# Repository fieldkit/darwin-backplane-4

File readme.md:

DARWIN-BACKPLANE

Experimental development repo for next-generation FieldKit hardware.

-- This hardware is experimental and still under development, the designs may contain errors. --

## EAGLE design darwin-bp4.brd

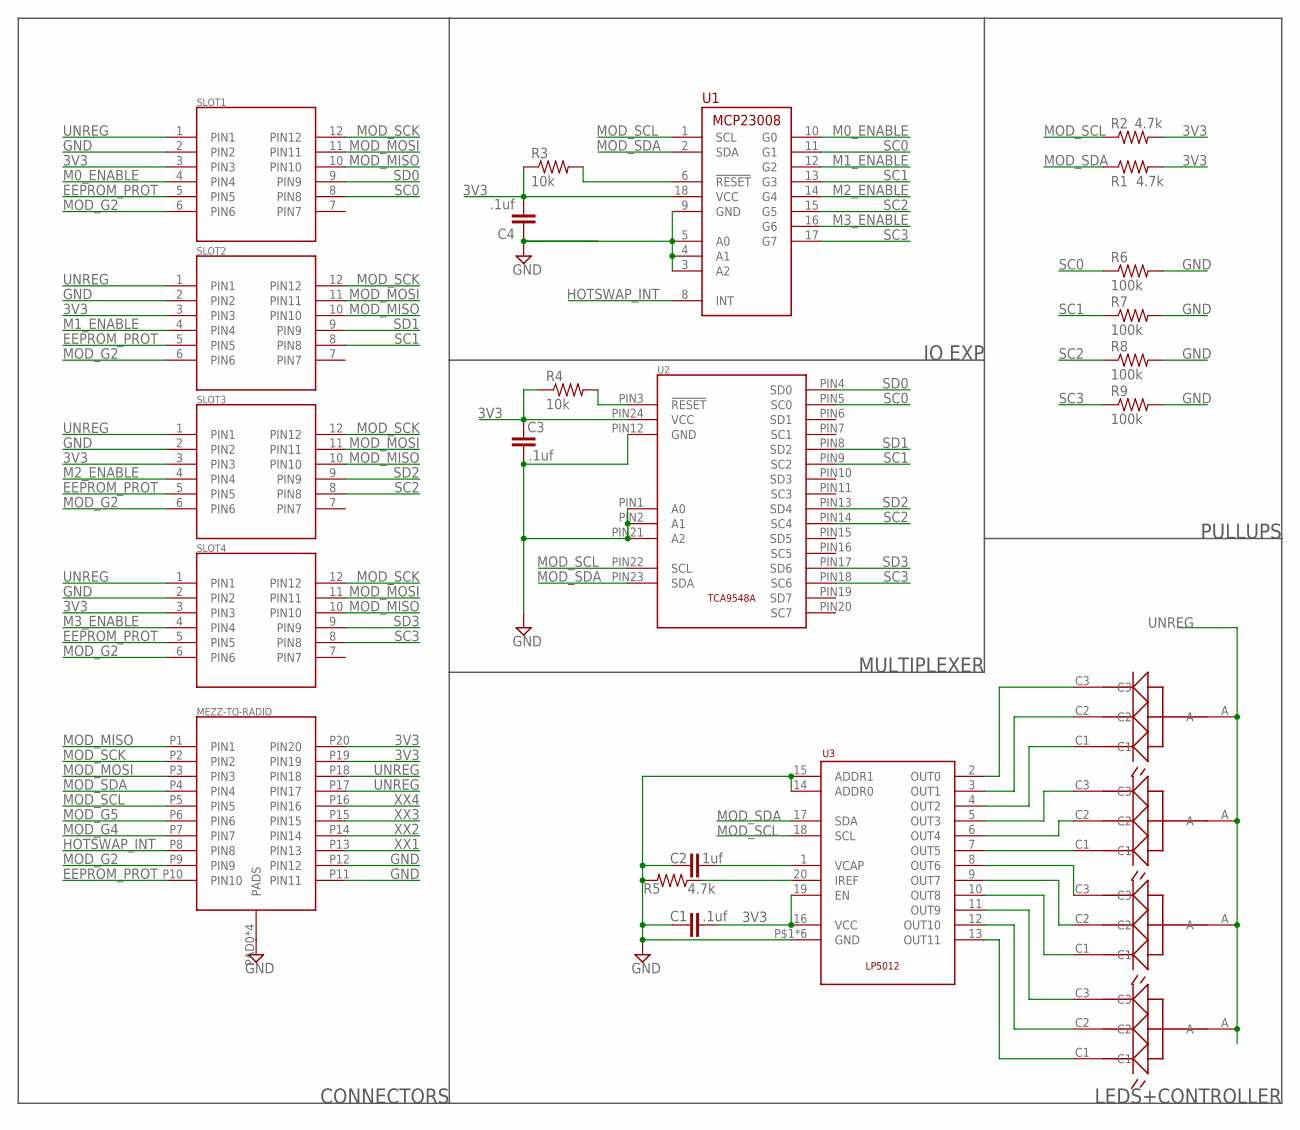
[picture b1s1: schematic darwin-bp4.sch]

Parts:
C1, C3, C4: .1uf; C0603K
C2: 1uf; C0603K
MEZZ-TO-RADIO: M55-6102042R7102(M); M55-7102042R
R1, R2, R5: 4.7k; R0603
R3, R4: 10k; R0603
R6, R7, R8, R9: 100k; R0603
SLOT1, SLOT2, SLOT3, SLOT4: 2X6-HEADERSDS; 12PH
U1: MCP23008; SOIC18-W
U2: TCA9548A; TSSOP-24
U3: LP5012; QFN40P300X300X80-20N
U$1, U$2, U$3, U$4: CLMVC-FKC-CGJJM569ABB7A343; 2MMPLCC4

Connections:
3V3: C1.2, C3.2, C4.2, MEZZ-TO-RADIO.P19 (PIN19), MEZZ-TO-RADIO.P20 (PIN20), R1.2, R2.2, R3.1, R4.1, SLOT1.3 (PIN3), SLOT2.3 (PIN3), SLOT3.3 (PIN3), SLOT4.3 (PIN3), U1.18 (VCC), U2.PIN24 (VCC), U3.16 (VCC), U3.19 (EN)
!RESET: R3.2, U1.6 (!RESET)
EEPROM_PROT: MEZZ-TO-RADIO.P10 (PIN10), SLOT1.5 (PIN5), SLOT2.5 (PIN5), SLOT3.5 (PIN5), SLOT4.5 (PIN5)
GND: C1.1, C2.1, C3.1, C4.1, MEZZ-TO-RADIO.P11 (PIN11), MEZZ-TO-RADIO.P12 (PIN12), MEZZ-TO-RADIO.PAD0 (PADS), MEZZ-TO-RADIO.PAD1 (PADS), MEZZ-TO-RADIO.PAD2 (PADS), MEZZ-TO-RADIO.PAD3 (PADS), R5.2, R6.2, R7.2, R8.2, R9.2, SLOT1.2 (PIN2), SLOT2.2 (PIN2), SLOT3.2 (PIN2), SLOT4.2 (PIN2), U1.3 (A2), U1.4 (A1), U1.5 (A0), U1.9 (GND), U2.PIN1 (A0), U2.PIN2 (A1), U2.PIN12 (GND), U2.PIN21 (A2), U3.14 (ADDR0), U3.15 (ADDR1), U3.P$1 (GND), U3.P$2 (GND), U3.P$3 (GND), U3.P$4 (GND), U3.P$5 (GND), U3.P$6 (GND)
HOTSWAP_INT: MEZZ-TO-RADIO.P8 (PIN8), U1.8 (INT)
M0_ENABLE: SLOT1.4 (PIN4), U1.10 (G0)
M1_ENABLE: SLOT2.4 (PIN4), U1.12 (G2)
M2_ENABLE: SLOT3.4 (PIN4), U1.14 (G4)
M3_ENABLE: SLOT4.4 (PIN4), U1.16 (G6)
MOD_G2: MEZZ-TO-RADIO.P9 (PIN9), SLOT1.6 (PIN6), SLOT2.6 (PIN6), SLOT3.6 (PIN6), SLOT4.6 (PIN6)
MOD_G4: MEZZ-TO-RADIO.P7 (PIN7)
MOD_G5: MEZZ-TO-RADIO.P6 (PIN6)
MOD_MISO: MEZZ-TO-RADIO.P1 (PIN1), SLOT1.10 (PIN10), SLOT2.10 (PIN10), SLOT3.10 (PIN10), SLOT4.10 (PIN10)
MOD_MOSI: MEZZ-TO-RADIO.P3 (PIN3), SLOT1.11 (PIN11), SLOT2.11 (PIN11), SLOT3.11 (PIN11), SLOT4.11 (PIN11)
MOD_SCK: MEZZ-TO-RADIO.P2 (PIN2), SLOT1.12 (PIN12), SLOT2.12 (PIN12), SLOT3.12 (PIN12), SLOT4.12 (PIN12)
MOD_SCL: MEZZ-TO-RADIO.P5 (PIN5), R2.1, U1.1 (SCL), U2.PIN22 (SCL), U3.18 (SCL)
MOD_SDA: MEZZ-TO-RADIO.P4 (PIN4), R1.1, U1.2 (SDA), U2.PIN23 (SDA), U3.17 (SDA)
unnamed: U3.2 (OUT0), U$1.C3
unnamed: R4.2, U2.PIN3 (!RESET)
unnamed: U3.3 (OUT1), U$1.C2
unnamed: U3.4 (OUT2), U$1.C1
unnamed: U3.5 (OUT3), U$2.C3
unnamed: U3.6 (OUT4), U$2.C2
unnamed: U3.7 (OUT5), U$2.C1
unnamed: U3.8 (OUT6), U$3.C3
unnamed: U3.9 (OUT7), U$3.C2
unnamed: U3.10 (OUT8), U$3.C1
unnamed: U3.11 (OUT9), U$4.C3
unnamed: U3.12 (OUT10), U$4.C2
unnamed: U3.13 (OUT11), U$4.C1
unnamed: C2.2, U3.1 (VCAP)
unnamed: R5.1, U3.20 (IREF)
SC0: R6.1, SLOT1.8 (PIN8), U1.11 (G1), U2.PIN5 (SC0)
SC1: R7.1, SLOT2.8 (PIN8), U1.13 (G3), U2.PIN9 (SC2)
SC2: R8.1, SLOT3.8 (PIN8), U1.15 (G5), U2.PIN14 (SC4)
SC3: R9.1, SLOT4.8 (PIN8), U1.17 (G7), U2.PIN18 (SC6)
SD0: SLOT1.9 (PIN9), U2.PIN4 (SD0)
SD1: SLOT2.9 (PIN9), U2.PIN8 (SD2)
SD2: SLOT3.9 (PIN9), U2.PIN13 (SD4)
SD3: SLOT4.9 (PIN9), U2.PIN17 (SD6)
UNREG: MEZZ-TO-RADIO.P17 (PIN17), MEZZ-TO-RADIO.P18 (PIN18), SLOT1.1 (PIN1), SLOT2.1 (PIN1), SLOT3.1 (PIN1), SLOT4.1 (PIN1), U$1.A, U$2.A, U$3.A, U$4.A
XX1: MEZZ-TO-RADIO.P13 (PIN13)
XX2: MEZZ-TO-RADIO.P14 (PIN14)
XX3: MEZZ-TO-RADIO.P15 (PIN15)
XX4: MEZZ-TO-RADIO.P16 (PIN16)

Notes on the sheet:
IO EXP
MULTIPLEXER
LEDS+CONTROLLER
PULLUPS
CONNECTORS

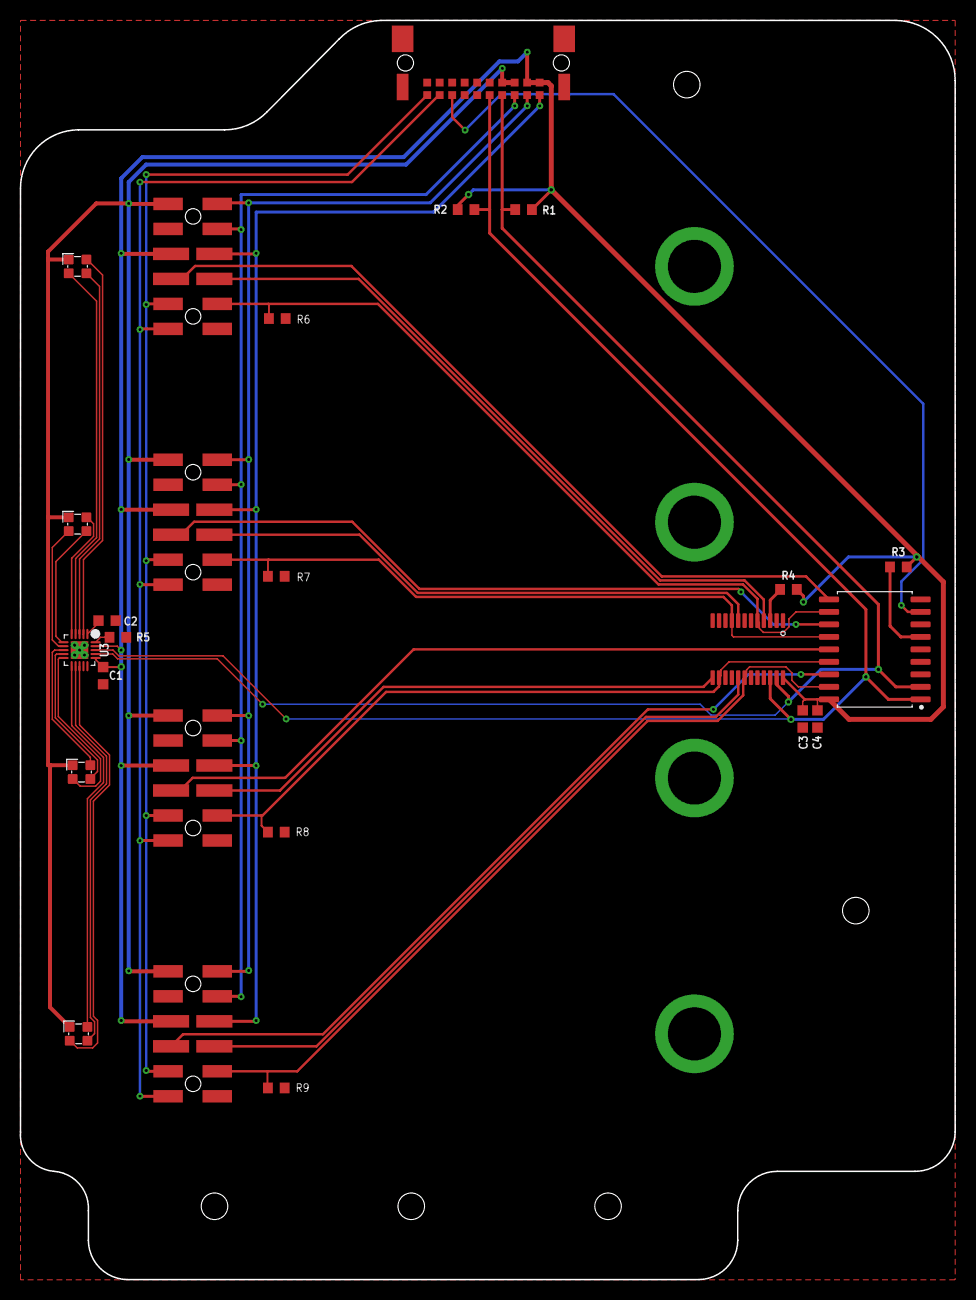
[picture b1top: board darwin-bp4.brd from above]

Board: 4 copper layers, 95.0 x 128.0 mm, 25 parts (0 on the bottom side), 39 nets.

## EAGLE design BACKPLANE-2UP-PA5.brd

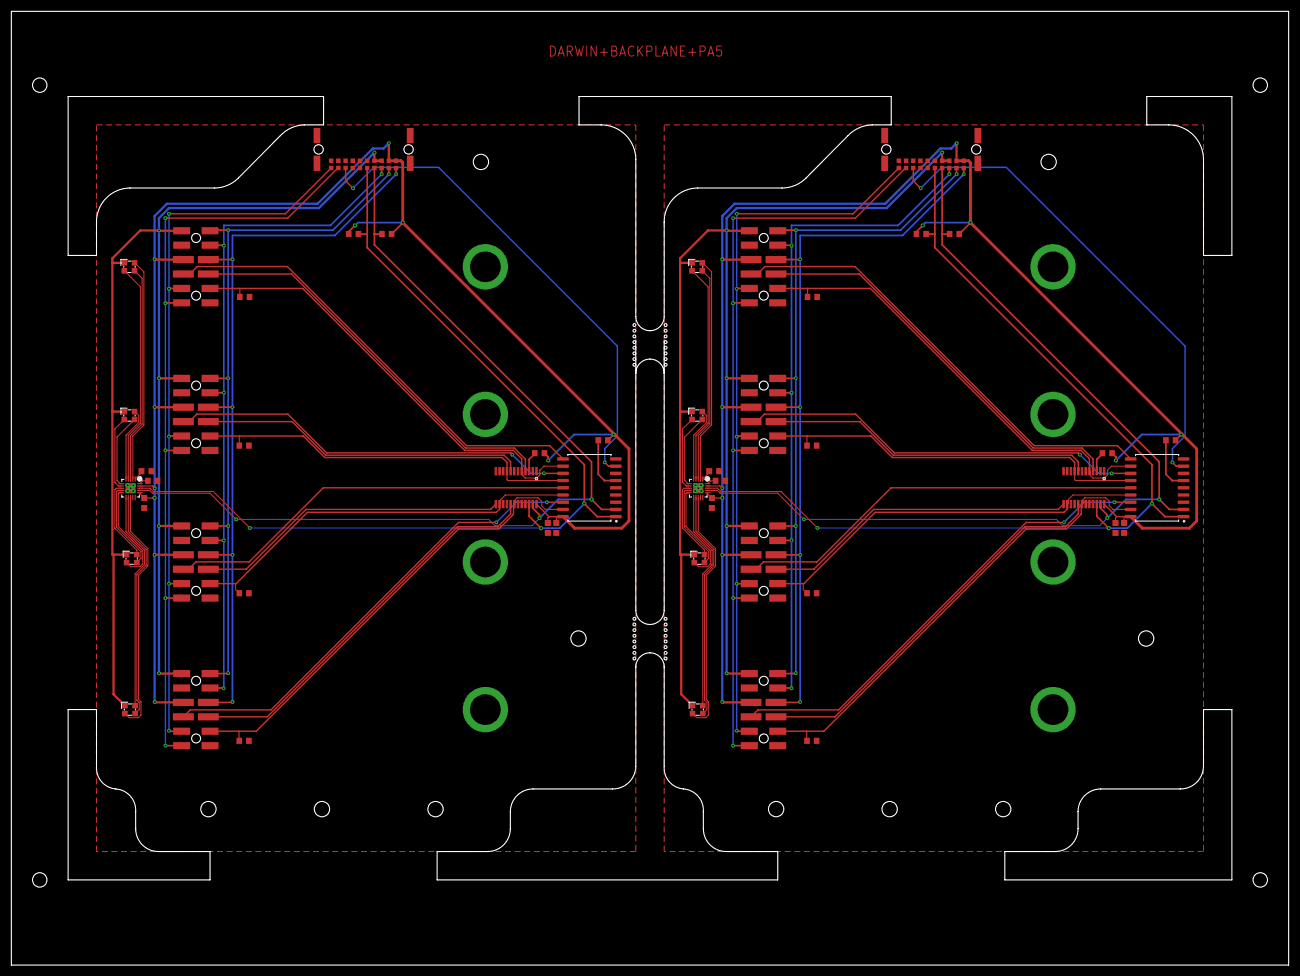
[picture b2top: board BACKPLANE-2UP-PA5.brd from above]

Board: 2 copper layers, 225.0 x 168.0 mm, 50 parts (0 on the bottom side), 78 nets.

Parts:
C1, C5: .1u; C0603K
C2, C6: 1u; C0603K
C3, C4, C7, C8: .1uf; C0603K
MEZZ-TO-RADIO, MEZZ-TO-RADIO1: M55-6102042R7102(M); M55-7102042R
R1, R2, R10, R11: 4.7k; R0603
R3, R4, R12, R13: 10k; R0603
R5, R14: R0603
R6, R7, R8, R9, R15, R16, R17, R18: 100k; R0603
SLOT1, SLOT2, SLOT3, SLOT4, SLOT5, SLOT6, SLOT7, SLOT8: 2X6-HEADERSDS; 12PH
U1, U4: MCP23008; SOIC18-W
U2, U5: TCA9548A; TSSOP-24
U3, U6: LP5012; QFN40P300X300X80-20N
U$1, U$2, U$3, U$4, U$5, U$6, U$7, U$8: CLMVC-FKC-CGJJM569ABB7A343; 2MMPLCC4

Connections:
3V1: C1.2, C3.2, C4.2, MEZZ-TO-RADIO.P19, MEZZ-TO-RADIO.P20, R1.2, R2.2, R3.1, R4.1, SLOT1.3, SLOT2.3, SLOT3.3, SLOT4.3, U1.18, U2.PIN24, U3.16, U3.19
3V2: C5.2, C7.2, C8.2, MEZZ-TO-RADIO1.P19, MEZZ-TO-RADIO1.P20, R10.2, R11.2, R12.1, R13.1, SLOT5.3, SLOT6.3, SLOT7.3, SLOT8.3, U4.18, U5.PIN24, U6.16, U6.19
!RESET: R3.2, U1.6
!RESET1: R12.2, U4.6
EEPROM_PROT1: MEZZ-TO-RADIO.P10, SLOT1.5, SLOT2.5, SLOT3.5, SLOT4.5
EEPROM_PROT2: MEZZ-TO-RADIO1.P10, SLOT5.5, SLOT6.5, SLOT7.5, SLOT8.5
GND: C1.1, C2.1, C3.1, C4.1, MEZZ-TO-RADIO.P11, MEZZ-TO-RADIO.P12, R5.2, R6.2, R7.2, R8.2, R9.2, SLOT1.2, SLOT2.2, SLOT3.2, SLOT4.2, U1.3, U1.4, U1.5, U1.9, U2.PIN1, U2.PIN2, U2.PIN12, U2.PIN21, U3.14, U3.15, U3.P$1, U3.P$2, U3.P$3, U3.P$4, U3.P$5, U3.P$6
GND1: C5.1, C6.1, C7.1, C8.1, MEZZ-TO-RADIO1.P11, MEZZ-TO-RADIO1.P12, R14.2, R15.2, R16.2, R17.2, R18.2, SLOT5.2, SLOT6.2, SLOT7.2, SLOT8.2, U4.3, U4.4, U4.5, U4.9, U5.PIN1, U5.PIN2, U5.PIN12, U5.PIN21, U6.14, U6.15, U6.P$1, U6.P$2, U6.P$3, U6.P$4, U6.P$5, U6.P$6
HOTSWAP_INT: MEZZ-TO-RADIO.P8, U1.8
HOTSWAP_INT1: MEZZ-TO-RADIO1.P8, U4.8
M0_ENABLE: SLOT1.4, U1.10
M0_ENABLE1: SLOT5.4, U4.10
M1_ENABLE: SLOT2.4, U1.12
M1_ENABLE1: SLOT6.4, U4.12
M2_ENABLE: SLOT3.4, U1.14
M2_ENABLE1: SLOT7.4, U4.14
M3_ENABLE: SLOT4.4, U1.16
M3_ENABLE1: SLOT8.4, U4.16
MOD_G1: MEZZ-TO-RADIO.P9, SLOT1.6, SLOT2.6, SLOT3.6, SLOT4.6
MOD_G3: MEZZ-TO-RADIO1.P9, SLOT5.6, SLOT6.6, SLOT7.6, SLOT8.6
MOD_MISO: MEZZ-TO-RADIO.P1, SLOT1.10, SLOT2.10, SLOT3.10, SLOT4.10
MOD_MISO1: MEZZ-TO-RADIO1.P1, SLOT5.10, SLOT6.10, SLOT7.10, SLOT8.10
MOD_MOSI: MEZZ-TO-RADIO.P3, SLOT1.11, SLOT2.11, SLOT3.11, SLOT4.11
MOD_MOSI1: MEZZ-TO-RADIO1.P3, SLOT5.11, SLOT6.11, SLOT7.11, SLOT8.11
MOD_SCK: MEZZ-TO-RADIO.P2, SLOT1.12, SLOT2.12, SLOT3.12, SLOT4.12
MOD_SCK1: MEZZ-TO-RADIO1.P2, SLOT5.12, SLOT6.12, SLOT7.12, SLOT8.12
MOD_SCL: MEZZ-TO-RADIO.P5, R2.1, U1.1, U2.PIN22, U3.18
MOD_SCL1: MEZZ-TO-RADIO1.P5, R11.1, U4.1, U5.PIN22, U6.18
MOD_SDA: MEZZ-TO-RADIO.P4, R1.1, U1.2, U2.PIN23, U3.17
MOD_SDA1: MEZZ-TO-RADIO1.P4, R10.1, U4.2, U5.PIN23, U6.17
unnamed: U3.2, U$1.C3
unnamed: R4.2, U2.PIN3
unnamed: U3.3, U$1.C2
unnamed: U3.4, U$1.C1
unnamed: U3.5, U$2.C3
unnamed: U3.6, U$2.C2
unnamed: U3.7, U$2.C1
unnamed: U3.8, U$3.C3
unnamed: U3.9, U$3.C2
unnamed: R13.2, U5.PIN3
unnamed: U3.10, U$3.C1
unnamed: U3.11, U$4.C3
unnamed: U3.12, U$4.C2
unnamed: U3.13, U$4.C1
unnamed: U6.2, U$5.C3
unnamed: U6.3, U$5.C2
unnamed: U6.4, U$5.C1
unnamed: U6.5, U$6.C3
unnamed: U6.6, U$6.C2
unnamed: C2.2, U3.1
unnamed: R5.1, U3.20
unnamed: U6.7, U$6.C1
unnamed: U6.8, U$7.C3
unnamed: U6.9, U$7.C2
unnamed: U6.10, U$7.C1
unnamed: U6.11, U$8.C3
unnamed: U6.12, U$8.C2
unnamed: U6.13, U$8.C1
unnamed: C6.2, U6.1
unnamed: R14.1, U6.20
SC0: R6.1, SLOT1.8, U1.11, U2.PIN5
SC1: R7.1, SLOT2.8, U1.13, U2.PIN9
SC2: R8.1, SLOT3.8, U1.15, U2.PIN14
SC3: R9.1, SLOT4.8, U1.17, U2.PIN18
SC4: R15.1, SLOT5.8, U4.11, U5.PIN5
SC5: R16.1, SLOT6.8, U4.13, U5.PIN9
SC6: R17.1, SLOT7.8, U4.15, U5.PIN14
SC7: R18.1, SLOT8.8, U4.17, U5.PIN18
SD0: SLOT1.9, U2.PIN4
SD1: SLOT2.9, U2.PIN8
SD2: SLOT3.9, U2.PIN13
SD3: SLOT4.9, U2.PIN17
SD4: SLOT5.9, U5.PIN4
SD5: SLOT8.9, U5.PIN17
SD6: SLOT7.9, U5.PIN13
SD7: SLOT6.9, U5.PIN8
UNREG: MEZZ-TO-RADIO.P17, MEZZ-TO-RADIO.P18, SLOT1.1, SLOT2.1, SLOT3.1, SLOT4.1, U$1.A, U$2.A, U$3.A, U$4.A
UNREG1: MEZZ-TO-RADIO1.P17, MEZZ-TO-RADIO1.P18, SLOT5.1, SLOT6.1, SLOT7.1, SLOT8.1, U$5.A, U$6.A, U$7.A, U$8.A

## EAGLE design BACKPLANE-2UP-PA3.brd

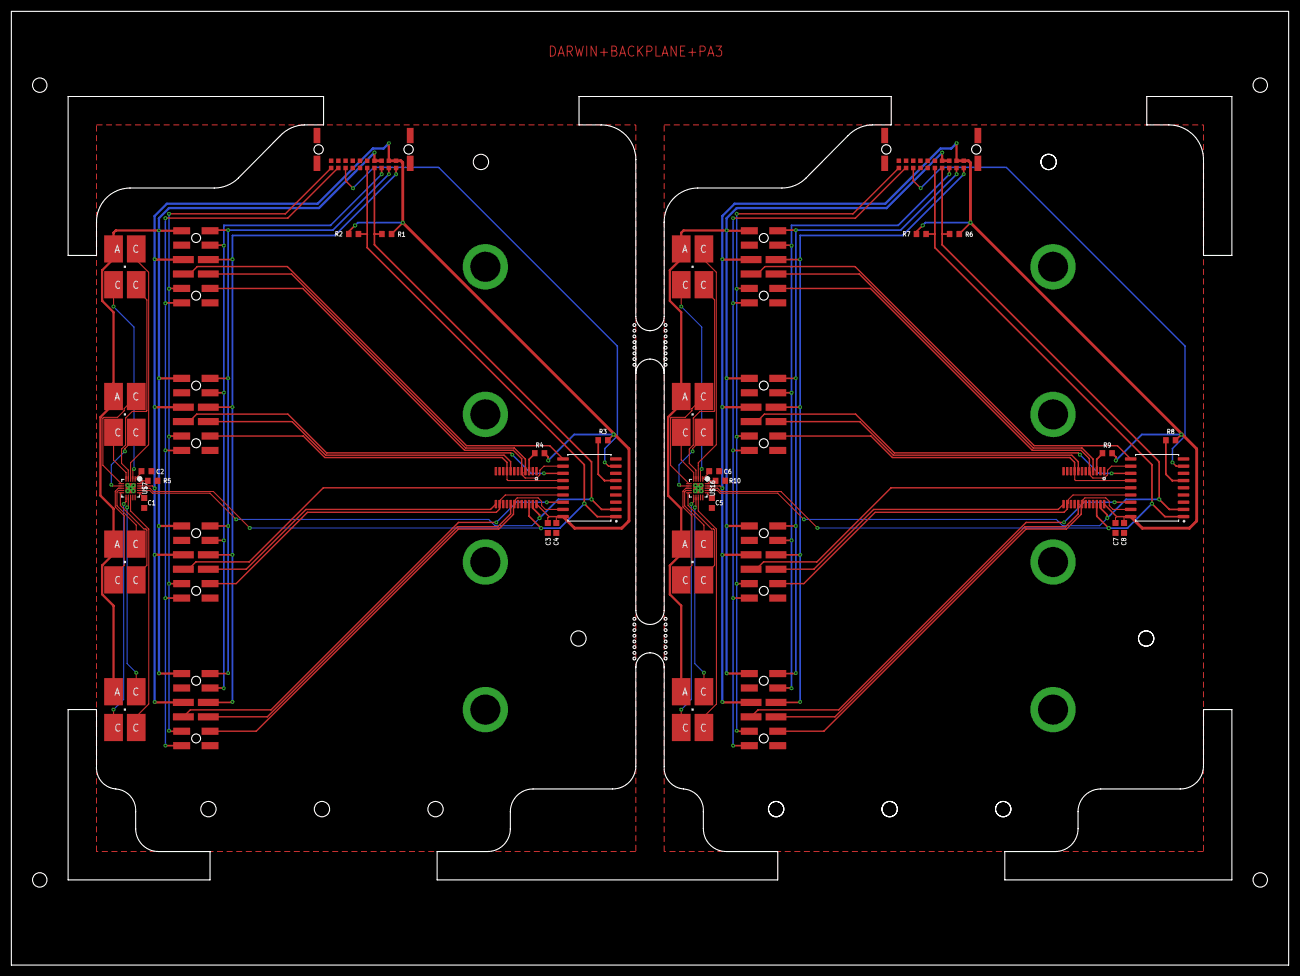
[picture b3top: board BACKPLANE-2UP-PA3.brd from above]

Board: 2 copper layers, 225.0 x 168.0 mm, 42 parts (0 on the bottom side), 78 nets.

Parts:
C1, C5: .1u; C0603K
C2, C3, C4, C6, C7, C8: 1u; C0603K
LED1, LED2, LED3, LED4, LED5, LED6, LED7, LED8: P-LCC-4
R1, R2, R6, R7: 4.7k; R0603
R3, R4, R8, R9: 10k; R0603
R5, R10: R0603
U$1, U$9: MCP23008; SOIC18-W
U$2, U$3, U$4, U$5, U$10, U$11, U$12, U$14: 2X6-HEADERSDS; 12PH
U$6, U$15: TCA9548A; TSSOP-24
U$7, U$16: LP5012; QFN40P300X300X80-20N
U$8, U$13: M55-6102042R7102(M); M55-7102042R

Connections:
3V1: C1.2, C3.2, C4.2, R1.2, R2.2, R3.1, R4.1, U$1.18, U$2.3, U$3.3, U$4.3, U$5.3, U$6.PIN24, U$7.16, U$7.19, U$13.P19, U$13.P20
3V2: C5.2, C7.2, C8.2, R6.2, R7.2, R8.1, R9.1, U$8.P19, U$8.P20, U$9.18, U$10.3, U$11.3, U$12.3, U$14.3, U$15.PIN24, U$16.16, U$16.19
!RESET: R3.2, U$1.6
!RESET1: R8.2, U$9.6
EEPROM_PROT1: U$2.5, U$3.5, U$4.5, U$5.5, U$13.P10
EEPROM_PROT2: U$8.P10, U$10.5, U$11.5, U$12.5, U$14.5
GND: C1.1, C2.1, C3.1, C4.1, R5.2, U$1.3, U$1.4, U$1.5, U$1.9, U$2.2, U$3.2, U$4.2, U$5.2, U$6.PIN1, U$6.PIN2, U$6.PIN12, U$6.PIN21, U$7.14, U$7.15, U$7.P$1, U$7.P$2, U$7.P$3, U$7.P$4, U$7.P$5, U$7.P$6, U$13.P11, U$13.P12
GND1: C5.1, C6.1, C7.1, C8.1, R10.2, U$8.P11, U$8.P12, U$9.3, U$9.4, U$9.5, U$9.9, U$10.2, U$11.2, U$12.2, U$14.2, U$15.PIN1, U$15.PIN2, U$15.PIN12, U$15.PIN21, U$16.14, U$16.15, U$16.P$1, U$16.P$2, U$16.P$3, U$16.P$4, U$16.P$5, U$16.P$6
HOTSWAP_INT: U$1.8, U$13.P8
HOTSWAP_INT1: U$8.P8, U$9.8
M0_ENABLE: U$1.10, U$2.4
M0_ENABLE1: U$9.10, U$10.4
M1_ENABLE: U$1.12, U$3.4
M1_ENABLE1: U$9.12, U$11.4
M2_ENABLE: U$1.14, U$4.4
M2_ENABLE1: U$9.14, U$12.4
M3_ENABLE: U$1.16, U$5.4
M3_ENABLE1: U$9.16, U$14.4
MOD_G1: U$2.6, U$3.6, U$4.6, U$5.6, U$13.P9
MOD_G3: U$8.P9, U$10.6, U$11.6, U$12.6, U$14.6
MOD_MISO: U$2.10, U$3.10, U$4.10, U$5.10, U$13.P1
MOD_MISO1: U$8.P1, U$10.10, U$11.10, U$12.10, U$14.10
MOD_MOSI: U$2.11, U$3.11, U$4.11, U$5.11, U$13.P3
MOD_MOSI1: U$8.P3, U$10.11, U$11.11, U$12.11, U$14.11
MOD_SCK: U$2.12, U$3.12, U$4.12, U$5.12, U$13.P2
MOD_SCK1: U$8.P2, U$10.12, U$11.12, U$12.12, U$14.12
MOD_SCL: R2.1, U$1.1, U$6.PIN22, U$7.18, U$13.P5
MOD_SCL1: R7.1, U$8.P5, U$9.1, U$15.PIN22, U$16.18
MOD_SDA: R1.1, U$1.2, U$6.PIN23, U$7.17, U$13.P4
MOD_SDA1: R6.1, U$8.P4, U$9.2, U$15.PIN23, U$16.17
unnamed: LED1.C@1, U$7.2
unnamed: R4.2, U$6.PIN3
unnamed: LED1.C@3, U$7.3
unnamed: LED1.C@4, U$7.4
unnamed: LED2.C@1, U$7.5
unnamed: LED2.C@3, U$7.6
unnamed: LED2.C@4, U$7.7
unnamed: LED3.C@1, U$7.8
unnamed: LED3.C@3, U$7.9
unnamed: R9.2, U$15.PIN3
unnamed: LED3.C@4, U$7.10
unnamed: LED4.C@1, U$7.11
unnamed: LED4.C@3, U$7.12
unnamed: LED4.C@4, U$7.13
unnamed: LED5.C@1, U$16.2
unnamed: LED5.C@3, U$16.3
unnamed: LED5.C@4, U$16.4
unnamed: LED6.C@1, U$16.5
unnamed: LED6.C@3, U$16.6
unnamed: C2.2, U$7.1
unnamed: R5.1, U$7.20
unnamed: LED6.C@4, U$16.7
unnamed: LED7.C@1, U$16.8
unnamed: LED7.C@3, U$16.9
unnamed: LED7.C@4, U$16.10
unnamed: LED8.C@1, U$16.11
unnamed: LED8.C@3, U$16.12
unnamed: LED8.C@4, U$16.13
unnamed: C6.2, U$16.1
unnamed: R10.1, U$16.20
SC0: U$1.11, U$2.8, U$6.PIN5
SC1: U$1.13, U$3.8, U$6.PIN9
SC2: U$1.15, U$4.8, U$6.PIN14
SC3: U$1.17, U$5.8, U$6.PIN18
SC4: U$9.11, U$10.8, U$15.PIN5
SC5: U$9.13, U$11.8, U$15.PIN9
SC6: U$9.15, U$12.8, U$15.PIN14
SC7: U$9.17, U$14.8, U$15.PIN18
SD0: U$2.9, U$6.PIN4
SD1: U$3.9, U$6.PIN8
SD2: U$4.9, U$6.PIN13
SD3: U$5.9, U$6.PIN17
SD4: U$10.9, U$15.PIN4
SD5: U$14.9, U$15.PIN17
SD6: U$12.9, U$15.PIN13
SD7: U$11.9, U$15.PIN8
UNREG: LED1.A, LED2.A, LED3.A, LED4.A, U$2.1, U$3.1, U$4.1, U$5.1, U$13.P17, U$13.P18
UNREG1: LED5.A, LED6.A, LED7.A, LED8.A, U$8.P17, U$8.P18, U$10.1, U$11.1, U$12.1, U$14.1

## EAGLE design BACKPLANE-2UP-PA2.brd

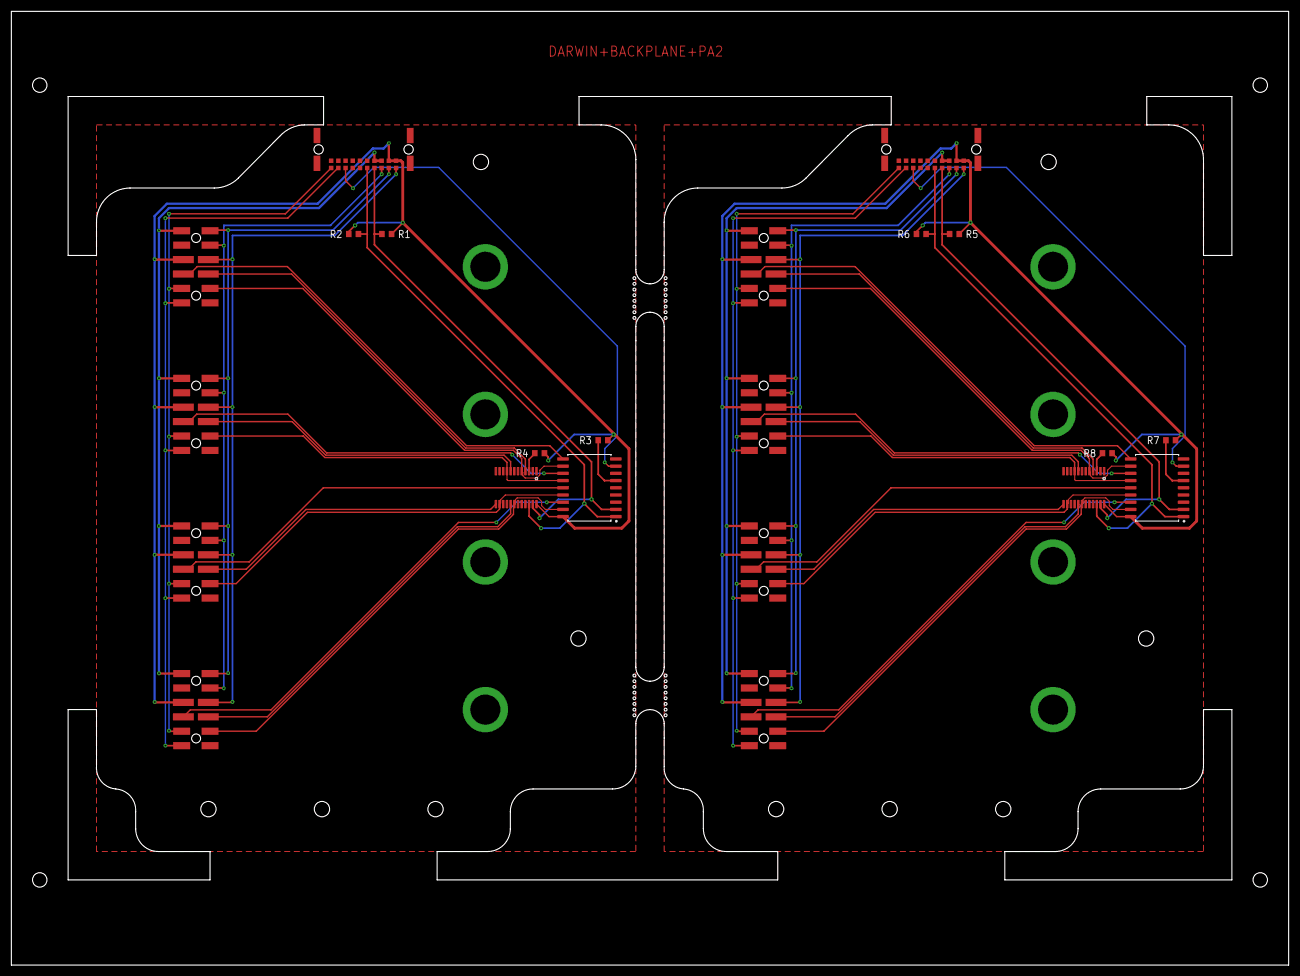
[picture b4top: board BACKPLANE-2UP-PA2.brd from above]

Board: 2 copper layers, 225.0 x 168.0 mm, 22 parts (0 on the bottom side), 50 nets.

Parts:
R1, R2, R3, R4, R5, R6, R7, R8: R0603
U$1, U$8: MCP23008; SOIC18-W
U$2, U$3, U$4, U$5, U$9, U$10, U$11, U$12: 2X6-HEADERSDS; 12PH
U$6, U$14: TCA9548A; TSSOP-24
U$7, U$13: M55-6102042R7102(M); M55-7102042R

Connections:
3V1: R5.2, R6.2, R7.1, R8.1, U$7.P19, U$7.P20, U$8.18, U$9.3, U$10.3, U$11.3, U$12.3, U$14.PIN24
3V3: R1.2, R2.2, R3.1, R4.1, U$1.18, U$2.3, U$3.3, U$4.3, U$5.3, U$6.PIN24, U$13.P19, U$13.P20
!RESET: R3.2, U$1.6
!RESET1: R7.2, U$8.6
EEPROM_PROT: U$2.5, U$3.5, U$4.5, U$5.5, U$13.P10
EEPROM_PROT1: U$7.P10, U$9.5, U$10.5, U$11.5, U$12.5
GND: U$1.3, U$1.4, U$1.5, U$1.9, U$2.2, U$3.2, U$4.2, U$5.2, U$6.PIN1, U$6.PIN2, U$6.PIN12, U$6.PIN21, U$13.P11, U$13.P12
GND1: U$7.P11, U$7.P12, U$8.3, U$8.4, U$8.5, U$8.9, U$9.2, U$10.2, U$11.2, U$12.2, U$14.PIN1, U$14.PIN2, U$14.PIN12, U$14.PIN21
HOTSWAP_INT: U$1.8, U$13.P8
HOTSWAP_INT1: U$7.P8, U$8.8
M0_ENABLE: U$1.10, U$2.4
M0_ENABLE1: U$8.10, U$9.4
M1_ENABLE: U$1.12, U$3.4
M1_ENABLE1: U$8.12, U$10.4
M2_ENABLE: U$1.14, U$4.4
M2_ENABLE1: U$8.14, U$11.4
M3_ENABLE: U$1.16, U$5.4
M3_ENABLE1: U$8.16, U$12.4
MOD_G1: U$7.P9, U$9.6, U$10.6, U$11.6, U$12.6
MOD_G2: U$2.6, U$3.6, U$4.6, U$5.6, U$13.P9
MOD_MISO: U$2.10, U$3.10, U$4.10, U$5.10, U$13.P1
MOD_MISO1: U$7.P1, U$9.10, U$10.10, U$11.10, U$12.10
MOD_MOSI: U$2.11, U$3.11, U$4.11, U$5.11, U$13.P3
MOD_MOSI1: U$7.P3, U$9.11, U$10.11, U$11.11, U$12.11
MOD_SCK: U$2.12, U$3.12, U$4.12, U$5.12, U$13.P2
MOD_SCK1: U$7.P2, U$9.12, U$10.12, U$11.12, U$12.12
MOD_SCL: R2.1, U$1.1, U$6.PIN22, U$13.P5
MOD_SCL1: R6.1, U$7.P5, U$8.1, U$14.PIN22
MOD_SDA: R1.1, U$1.2, U$6.PIN23, U$13.P4
MOD_SDA1: R5.1, U$7.P4, U$8.2, U$14.PIN23
unnamed: R8.2, U$14.PIN3
unnamed: R4.2, U$6.PIN3
SC0: U$1.11, U$2.8, U$6.PIN5
SC1: U$1.13, U$3.8, U$6.PIN9
SC2: U$1.15, U$4.8, U$6.PIN14
SC3: U$1.17, U$5.8, U$6.PIN18
SC4: U$8.11, U$9.8, U$14.PIN5
SC5: U$8.13, U$10.8, U$14.PIN9
SC6: U$8.15, U$11.8, U$14.PIN14
SC7: U$8.17, U$12.8, U$14.PIN18
SD0: U$2.9, U$6.PIN4
SD1: U$3.9, U$6.PIN8
SD2: U$4.9, U$6.PIN13
SD3: U$5.9, U$6.PIN17
SD4: U$9.9, U$14.PIN4
SD5: U$12.9, U$14.PIN17
SD6: U$11.9, U$14.PIN13
SD7: U$10.9, U$14.PIN8
UNREG: U$2.1, U$3.1, U$4.1, U$5.1, U$13.P17, U$13.P18
UNREG1: U$7.P17, U$7.P18, U$9.1, U$10.1, U$11.1, U$12.1

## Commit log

2019-07-17 Test Article 2
2019-09-16 Panelization. Production Articles 1 and 2.
2019-09-16 Added LEDs and decoupling.
2019-09-30 Cleanup.
2019-09-30 added readme
2019-10-17 Fixed LED footprints and tidied routing.
2020-01-16 Updated LED footprint, cleaned up routing, new production panel.
2020-02-11 Fixed power to LED controller, added pulldowns on hot swap detection pins, adjusted standoff holes.
2020-05-01 Cleaned up schematic and added PDF.
2020-05-01 Fixed updated connector footprint.
